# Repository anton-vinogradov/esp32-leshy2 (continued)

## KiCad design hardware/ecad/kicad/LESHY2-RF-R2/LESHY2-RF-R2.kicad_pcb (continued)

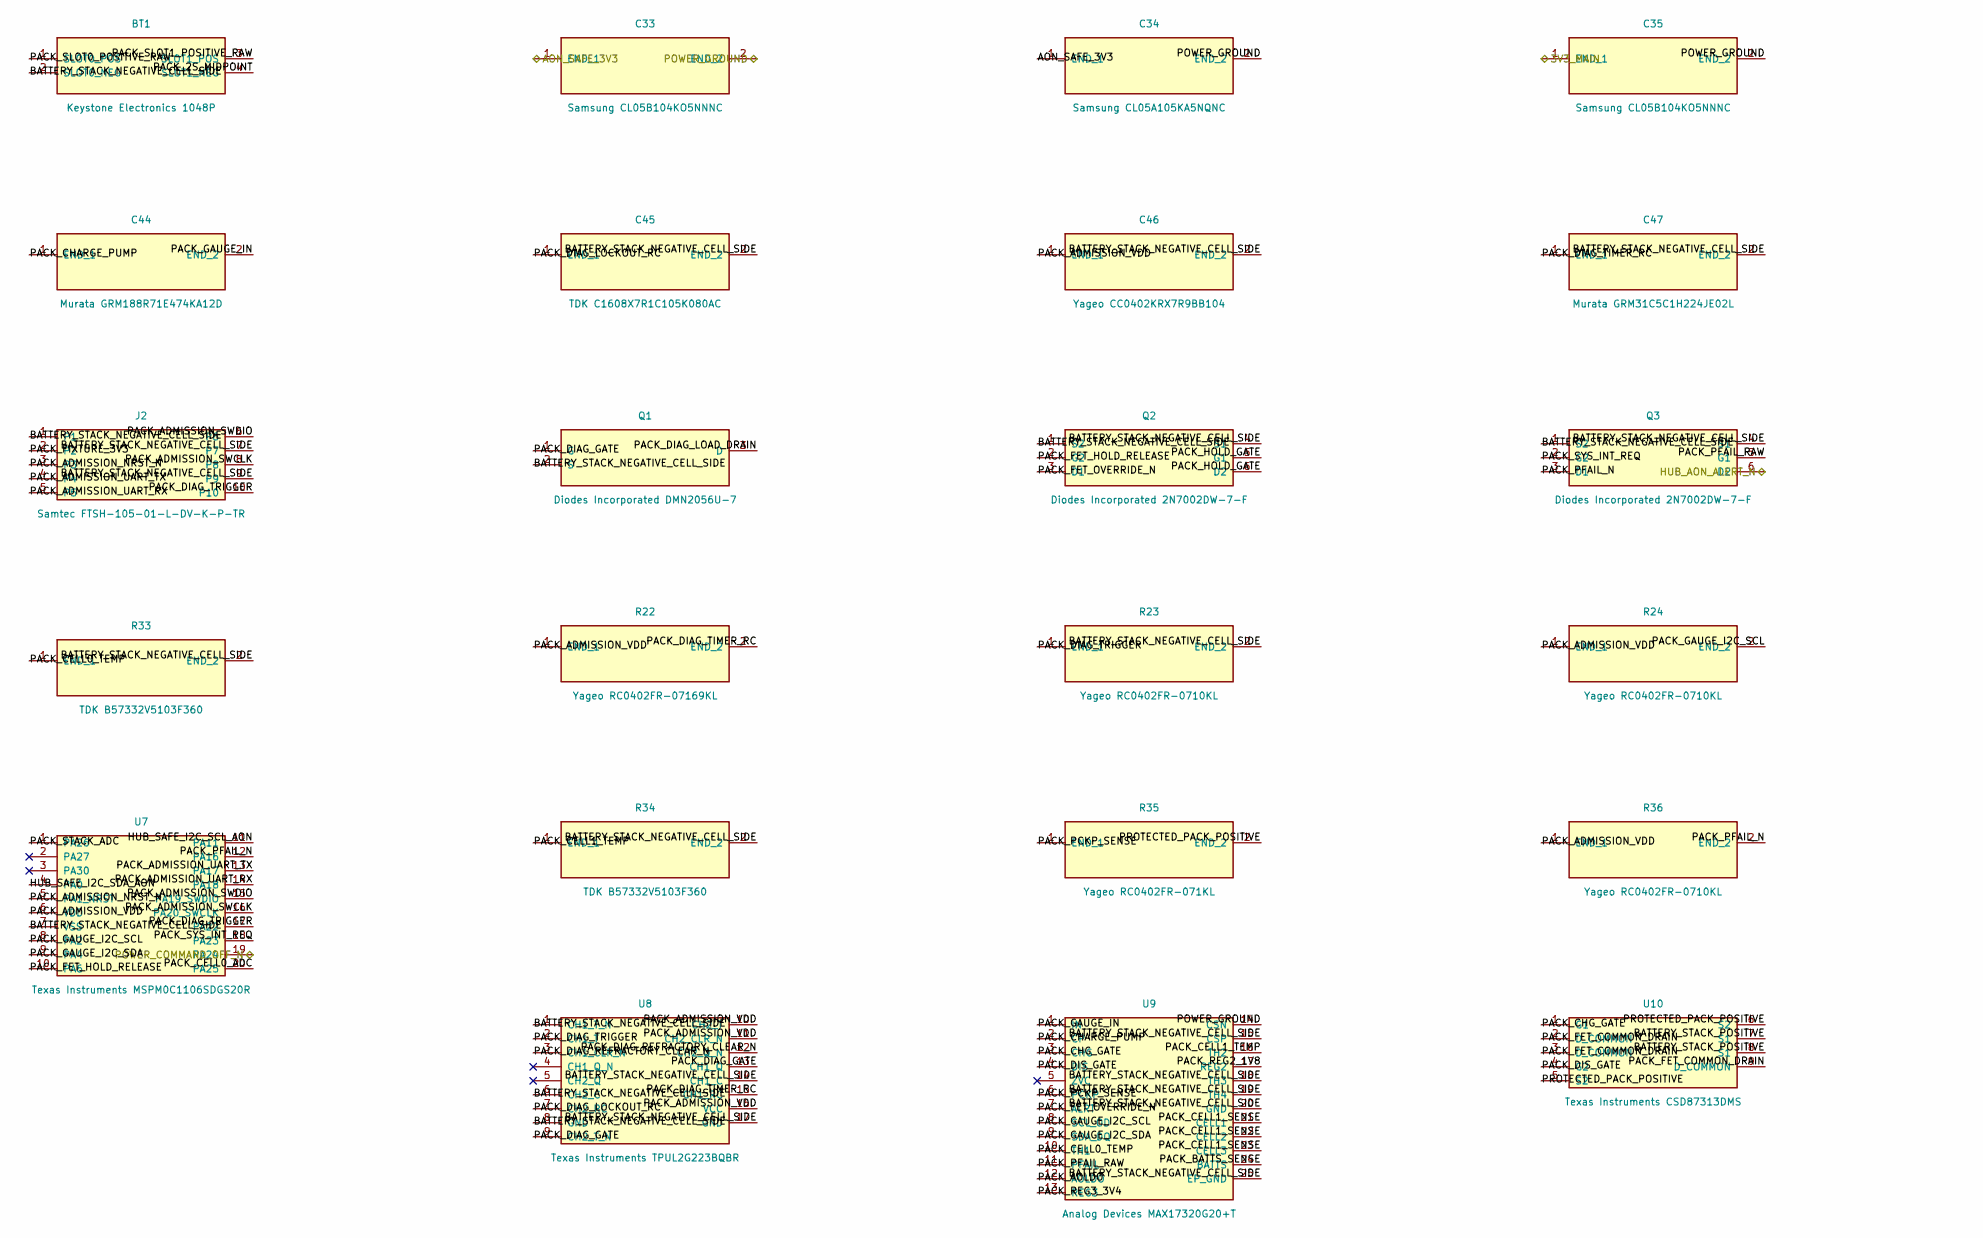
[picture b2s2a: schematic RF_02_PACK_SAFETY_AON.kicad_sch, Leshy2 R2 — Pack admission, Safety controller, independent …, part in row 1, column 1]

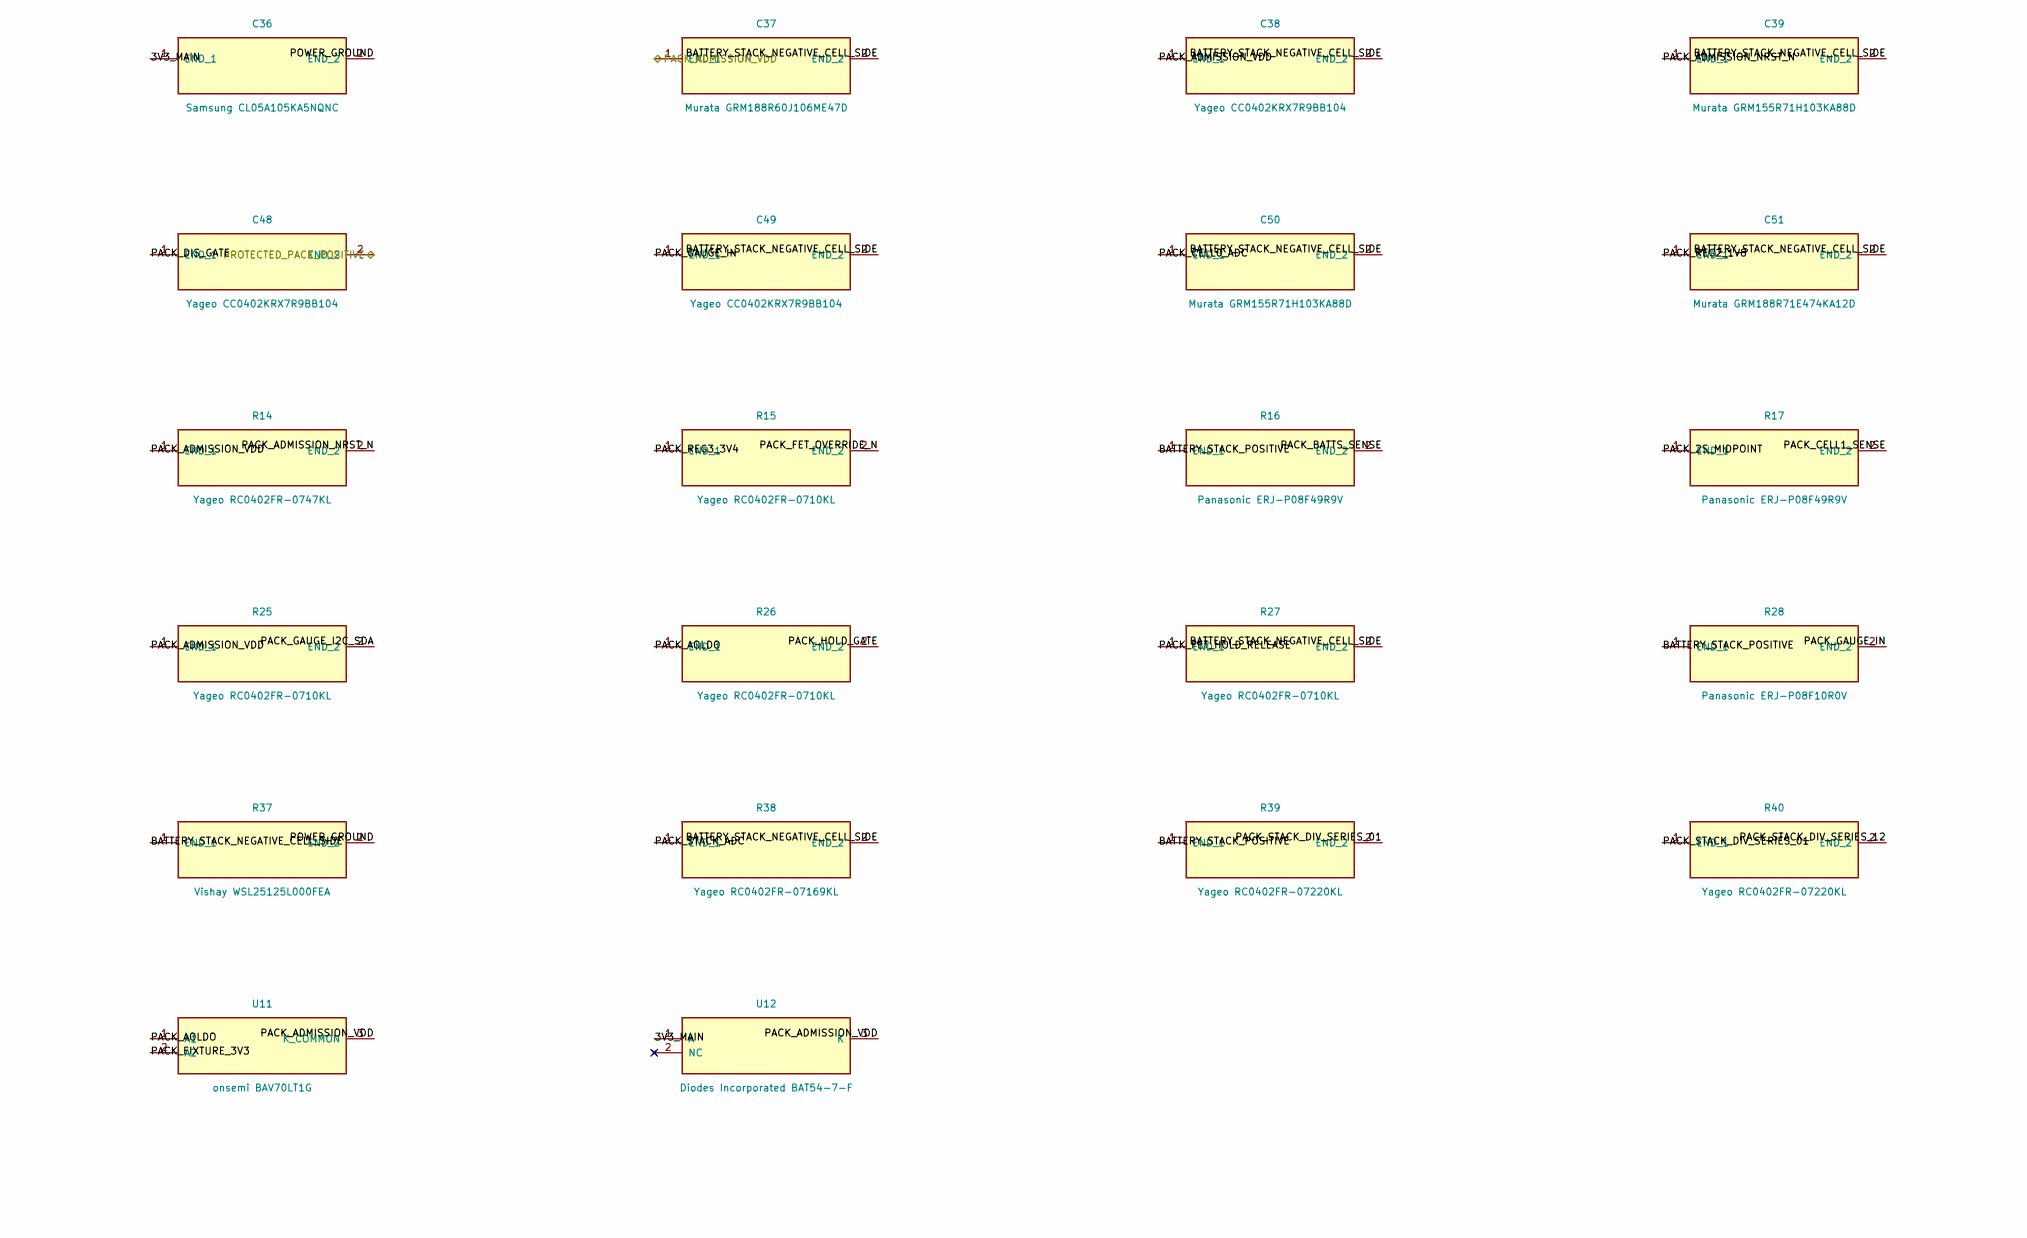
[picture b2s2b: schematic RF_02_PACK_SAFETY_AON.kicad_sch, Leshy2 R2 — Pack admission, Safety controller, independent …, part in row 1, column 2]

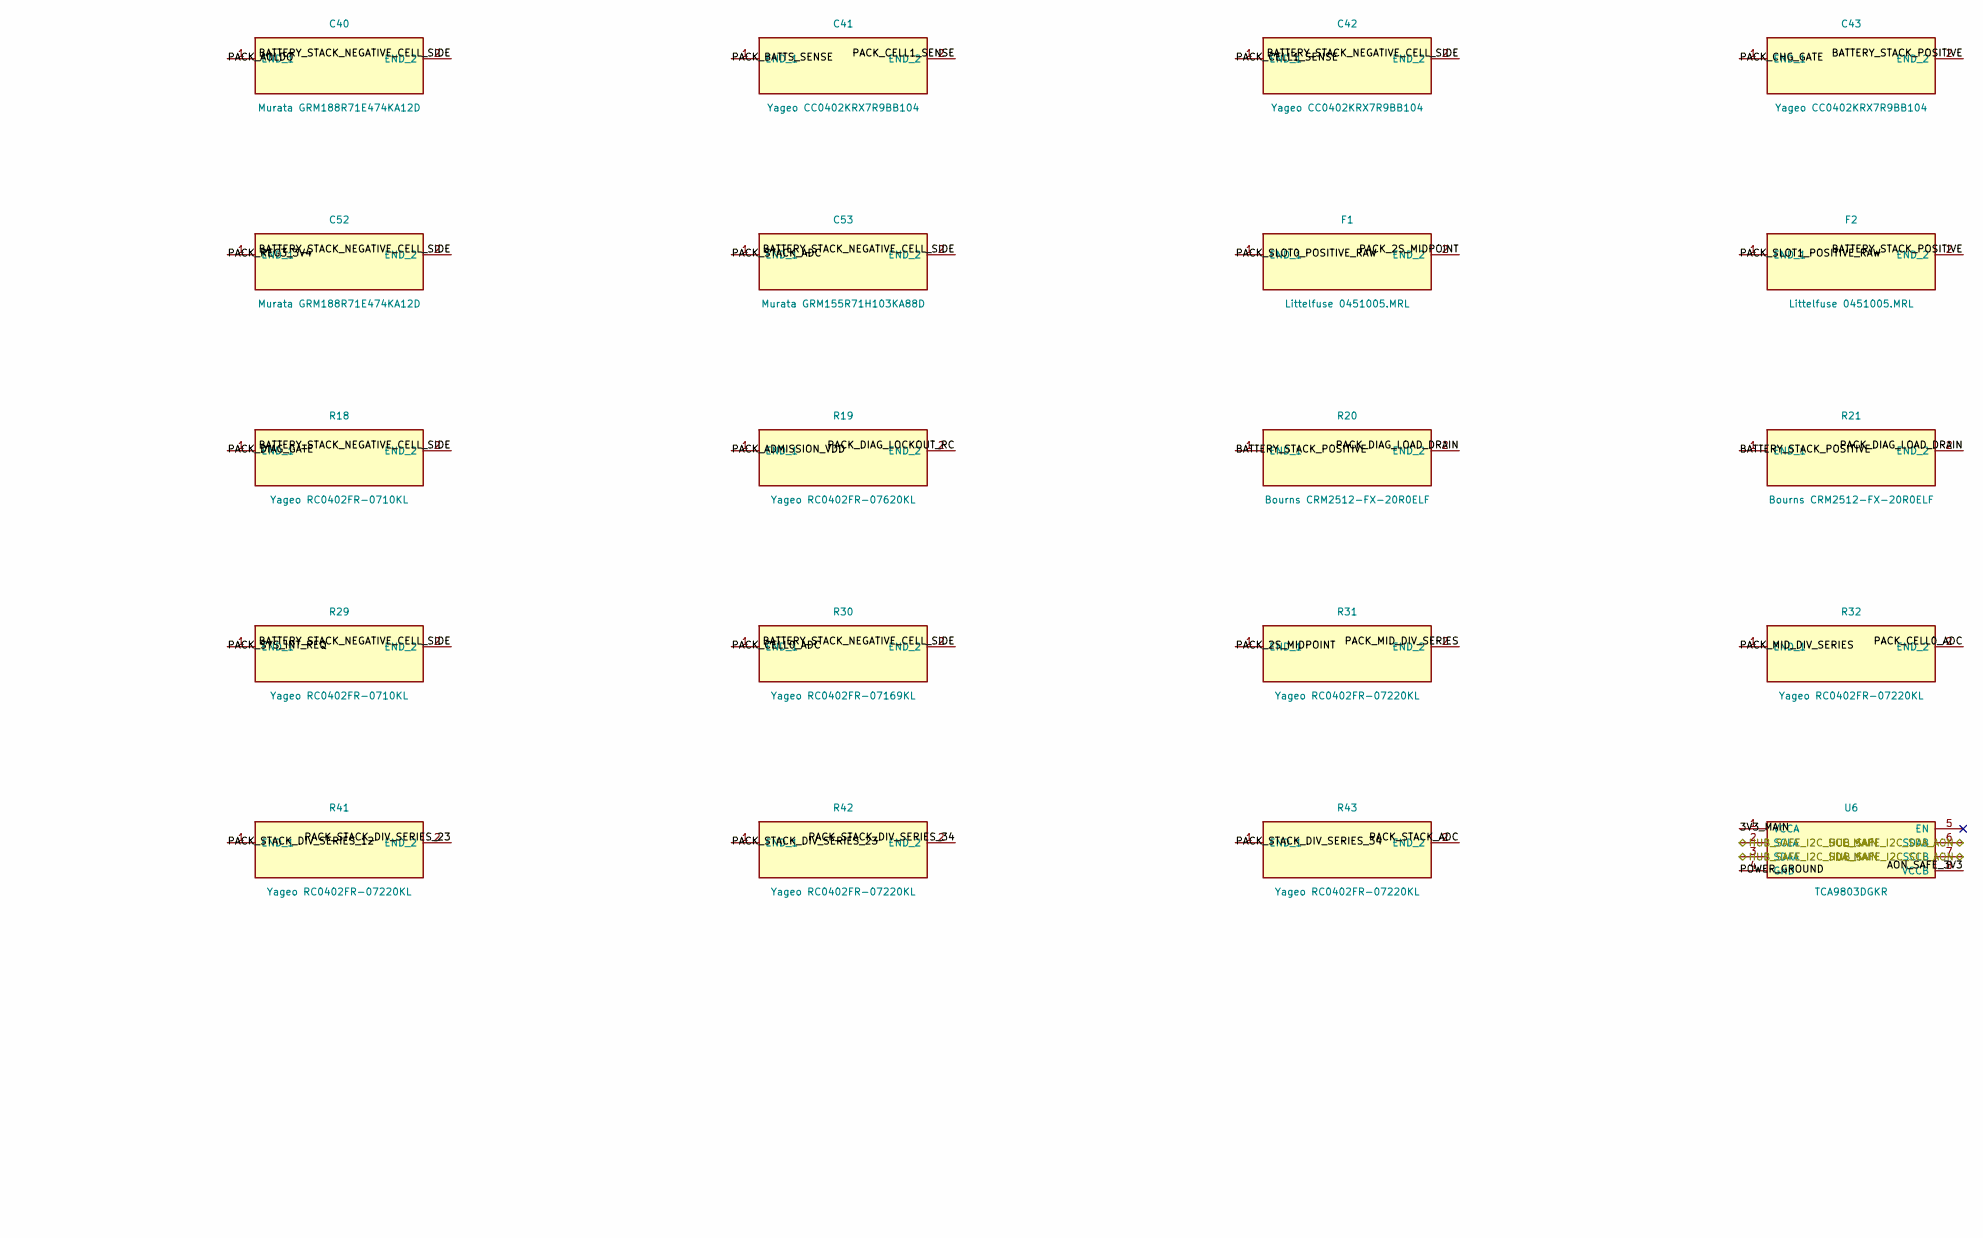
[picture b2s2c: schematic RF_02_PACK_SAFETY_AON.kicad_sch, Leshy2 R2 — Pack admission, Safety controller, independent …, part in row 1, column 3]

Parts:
BT1: Keystone Electronics 1048P; Keystone-1048P-POLARITY-CORRECTED
C33, C35: Samsung CL05B104KO5NNNC; C_0402_1005Metric
C34, C36: Samsung CL05A105KA5NQNC; C_0402_1005Metric
C37: Murata GRM188R60J106ME47D; C_0603_1608Metric
C38, C41, C42, C43, C46, C48, C49: Yageo CC0402KRX7R9BB104; C_0402_1005Metric
C39, C50, C53: Murata GRM155R71H103KA88D; C_0402_1005Metric
C40, C44, C51, C52: Murata GRM188R71E474KA12D; C_0603_1608Metric
C45: TDK C1608X7R1C105K080AC; C_0603_1608Metric
C47: Murata GRM31C5C1H224JE02L; C_1206_3216Metric
F1, F2: Littelfuse 0451005.MRL; 0451005.MRL
J2: Samtec FTSH-105-01-L-DV-K-P-TR; FTSH-105-01-L-DV-K-P-TR
Q1: Diodes Incorporated DMN2056U-7; SOT-23
Q2, Q3: Diodes Incorporated 2N7002DW-7-F; SOT-363_SC-70-6
R14: Yageo RC0402FR-0747KL; R_0402_1005Metric
R15, R18, R23, R24, R25, R26, R27, R29, R36: Yageo RC0402FR-0710KL; R_0402_1005Metric
R16, R17: Panasonic ERJ-P08F49R9V; R_1206_3216Metric
R19: Yageo RC0402FR-07620KL; R_0402_1005Metric
R20, R21: Bourns CRM2512-FX-20R0ELF; R_2512_6332Metric
R22, R30, R38: Yageo RC0402FR-07169KL; R_0402_1005Metric
R28: Panasonic ERJ-P08F10R0V; R_1206_3216Metric
R31, R32, R39, R40, R41, R42, R43: Yageo RC0402FR-07220KL; R_0402_1005Metric
R33, R34: TDK B57332V5103F360; R_0603_1608Metric
R35: Yageo RC0402FR-071KL; R_0402_1005Metric
R37: Vishay WSL25125L000FEA; R_2512_6332Metric
U6: TCA9803DGKR; VSSOP-8_3x3mm_P0.65mm
U7: Texas Instruments MSPM0C1106SDGS20R; Texas_DGS0020A_TSSOP-20_3x5.1mm_P0.5mm
U8: Texas Instruments TPUL2G223BQBR; TPUL2G223BQBR
U9: Analog Devices MAX17320G20+T; TQFN-24-1EP_4x4mm_P0.5mm_EP2.6x2.6mm
U10: Texas Instruments CSD87313DMS; CSD87313DMS
U11: onsemi BAV70LT1G; SOT-23
U12: Diodes Incorporated BAT54-7-F; SOT-23

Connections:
/RF_01_USB_PD_CHARGE/AON_SAFE_3V3: C33.1 (END_1), C34.1 (END_1), U6.8 (VCCB); also elsewhere on the board
/RF_01_USB_PD_CHARGE/POWER_GROUND: C33.2 (END_2), C34.2 (END_2), C35.2 (END_2), C36.2 (END_2), R37.2 (END_2), U6.4 (GND), U9.14 (CSN); also elsewhere on the board
/RF_01_USB_PD_CHARGE/PROTECTED_PACK_POSITIVE: C48.2 (END_2), R35.2 (END_2), U10.5 (S2), U10.6 (S2); also elsewhere on the board
/RF_02_PACK_SAFETY_AON/3V3_MAIN: C35.1 (END_1), C36.1 (END_1), U6.1 (VCCA), U12.1 (A); also elsewhere on the board
/RF_02_PACK_SAFETY_AON/BATTERY_STACK_NEGATIVE_CELL_SIDE: BT1.2 (SLOT0_NEG), C37.2 (END_2), C38.2 (END_2), C39.2 (END_2), C40.2 (END_2), C42.2 (END_2), C45.2 (END_2), C46.2 (END_2), C47.2 (END_2), C49.2 (END_2), C50.2 (END_2), C51.2 (END_2), C52.2 (END_2), C53.2 (END_2), J2.1, J2.7, J2.9, Q1.2 (S), Q2.1 (S2), Q2.4 (S1), Q3.1 (S2), Q3.4 (S1), R18.2 (END_2), R23.2 (END_2), R27.2 (END_2), R29.2 (END_2), R30.2 (END_2), R33.2 (END_2), R34.2 (END_2), R37.1 (END_1), R38.2 (END_2), U7.7 (VSS), U8.1 (CH1_T_N), U8.6 (CH2_C), U8.8 (GND), U8.14 (CH1_C), U8.17 (GND), U9.15 (CSP), U9.18 (TH3), U9.19 (TH4), U9.20 (GND), U9.25 (EP_GND)
/RF_02_PACK_SAFETY_AON/BATTERY_STACK_POSITIVE: C43.2 (END_2), F2.2 (END_2), R16.1 (END_1), R20.1 (END_1), R21.1 (END_1), R28.1 (END_1), R39.1 (END_1), U10.7 (S1), U10.8 (S1)
/RF_02_PACK_SAFETY_AON/HUB_SAFE_I2C_SCL_AON: U6.7 (SCLB), U7.11 (PA11); also elsewhere on the board
/RF_02_PACK_SAFETY_AON/HUB_SAFE_I2C_SCL_MAIN: U6.2 (SCLA); also elsewhere on the board
/RF_02_PACK_SAFETY_AON/HUB_SAFE_I2C_SDA_AON: U6.6 (SDAB), U7.4 (PA0); also elsewhere on the board
/RF_02_PACK_SAFETY_AON/HUB_SAFE_I2C_SDA_MAIN: U6.3 (SDAA); also elsewhere on the board
/RF_02_PACK_SAFETY_AON/PACK_2S_MIDPOINT: BT1.4 (SLOT1_NEG), F1.2 (END_2), R17.1 (END_1), R31.1 (END_1)
/RF_02_PACK_SAFETY_AON/PACK_ADMISSION_NRST_N: C39.1 (END_1), J2.3, R14.2 (END_2), U7.5 (PA1_NRST)
/RF_02_PACK_SAFETY_AON/PACK_ADMISSION_SWCLK: J2.8, U7.16 (PA20_SWCLK)
/RF_02_PACK_SAFETY_AON/PACK_ADMISSION_SWDIO: J2.6, U7.15 (PA19_SWDIO)
/RF_02_PACK_SAFETY_AON/PACK_ADMISSION_UART_RX: J2.5, U7.14 (PA18)
/RF_02_PACK_SAFETY_AON/PACK_ADMISSION_UART_TX: J2.4, U7.13 (PA17)
/RF_02_PACK_SAFETY_AON/PACK_ADMISSION_VDD: C37.1 (END_1), C38.1 (END_1), C46.1 (END_1), R14.1 (END_1), R19.1 (END_1), R22.1 (END_1), R24.1 (END_1), R25.1 (END_1), R36.1 (END_1), U7.6 (VDD), U8.10 (CH2_T), U8.11 (CH2_CLR_N), U8.16 (VCC), U11.3 (K_COMMON), U12.3 (K); also elsewhere on the board
/RF_02_PACK_SAFETY_AON/PACK_AOLDO: C40.1 (END_1), R26.1 (END_1), U9.12 (AOLDO), U11.1 (A1)
/RF_02_PACK_SAFETY_AON/PACK_BATTS_SENSE: C41.1 (END_1), R16.2 (END_2), U9.24 (BATTS)
/RF_02_PACK_SAFETY_AON/PACK_CELL0_ADC: C50.1 (END_1), R30.1 (END_1), R32.2 (END_2), U7.20 (PA25)
/RF_02_PACK_SAFETY_AON/PACK_CELL0_TEMP: R33.1 (END_1), U9.10 (TH1)
/RF_02_PACK_SAFETY_AON/PACK_CELL1_SENSE: C41.2 (END_2), C42.1 (END_1), R17.2 (END_2), U9.21 (CELL1), U9.22 (CELL2), U9.23 (CELL3)
/RF_02_PACK_SAFETY_AON/PACK_CELL1_TEMP: R34.1 (END_1), U9.16 (TH2)
/RF_02_PACK_SAFETY_AON/PACK_CHARGE_PUMP: C44.1 (END_1), U9.2 (CP)
/RF_02_PACK_SAFETY_AON/PACK_CHG_GATE: C43.1 (END_1), U9.3 (CHG), U10.1 (G1)
/RF_02_PACK_SAFETY_AON/PACK_DIAG_GATE: Q1.1 (G), R18.1 (END_1), U8.9 (CH2_T_N), U8.13 (CH1_Q)
/RF_02_PACK_SAFETY_AON/PACK_DIAG_LOAD_DRAIN: Q1.3 (D), R20.2 (END_2), R21.2 (END_2)
/RF_02_PACK_SAFETY_AON/PACK_DIAG_LOCKOUT_RC: C45.1 (END_1), R19.2 (END_2), U8.7 (CH2_RC)
/RF_02_PACK_SAFETY_AON/PACK_DIAG_REFRACTORY_CLEAR_N: U8.3 (CH1_CLR_N), U8.12 (CH2_Q_N)
/RF_02_PACK_SAFETY_AON/PACK_DIAG_TIMER_RC: C47.1 (END_1), R22.2 (END_2), U8.15 (CH1_RC)
/RF_02_PACK_SAFETY_AON/PACK_DIAG_TRIGGER: J2.10, R23.1 (END_1), U7.17 (PA22), U8.2 (CH1_T)
/RF_02_PACK_SAFETY_AON/PACK_DIS_GATE: C48.1 (END_1), U9.4 (DIS), U10.4 (G2)
/RF_02_PACK_SAFETY_AON/PACK_FET_COMMON_DRAIN: U10.2 (D_COMMON), U10.3 (D_COMMON), U10.9 (D_COMMON)
/RF_02_PACK_SAFETY_AON/PACK_FET_HOLD_RELEASE: Q2.2 (G2), R27.1 (END_1), U7.10 (PA6)
/RF_02_PACK_SAFETY_AON/PACK_FET_OVERRIDE_N: Q2.3 (D1), R15.2 (END_2), U9.7 (ALRT)
/RF_02_PACK_SAFETY_AON/PACK_FIXTURE_3V3: J2.2, U11.2 (A2)
/RF_02_PACK_SAFETY_AON/PACK_GAUGE_I2C_SCL: R24.2 (END_2), U7.8 (PA2), U9.8 (SCL_OD)
/RF_02_PACK_SAFETY_AON/PACK_GAUGE_I2C_SDA: R25.2 (END_2), U7.9 (PA4), U9.9 (SDA_DQ)
/RF_02_PACK_SAFETY_AON/PACK_GAUGE_IN: C44.2 (END_2), C49.1 (END_1), R28.2 (END_2), U9.1 (IN)
/RF_02_PACK_SAFETY_AON/PACK_HOLD_GATE: Q2.5 (G1), Q2.6 (D2), R26.2 (END_2)
/RF_02_PACK_SAFETY_AON/PACK_MID_DIV_SERIES: R31.2 (END_2), R32.1 (END_1)
/RF_02_PACK_SAFETY_AON/PACK_PCKP_SENSE: R35.1 (END_1), U9.6 (PCKP)
/RF_02_PACK_SAFETY_AON/PACK_PFAIL_N: Q3.3 (D1), R36.2 (END_2), U7.12 (PA16)
/RF_02_PACK_SAFETY_AON/PACK_PFAIL_RAW: Q3.5 (G1), U9.11 (PFAIL)
/RF_02_PACK_SAFETY_AON/PACK_REG2_1V8: C51.1 (END_1), U9.17 (REG2)
/RF_02_PACK_SAFETY_AON/PACK_REG3_3V4: C52.1 (END_1), R15.1 (END_1), U9.13 (REG3)
/RF_02_PACK_SAFETY_AON/PACK_SLOT0_POSITIVE_RAW: BT1.1 (SLOT0_POS), F1.1 (END_1)
/RF_02_PACK_SAFETY_AON/PACK_SLOT1_POSITIVE_RAW: BT1.3 (SLOT1_POS), F2.1 (END_1)
/RF_02_PACK_SAFETY_AON/PACK_STACK_ADC: C53.1 (END_1), R38.1 (END_1), R43.2 (END_2), U7.1 (PA26)
/RF_02_PACK_SAFETY_AON/PACK_STACK_DIV_SERIES_01: R39.2 (END_2), R40.1 (END_1)
/RF_02_PACK_SAFETY_AON/PACK_STACK_DIV_SERIES_12: R40.2 (END_2), R41.1 (END_1)
/RF_02_PACK_SAFETY_AON/PACK_STACK_DIV_SERIES_23: R41.2 (END_2), R42.1 (END_1)
/RF_02_PACK_SAFETY_AON/PACK_STACK_DIV_SERIES_34: R42.2 (END_2), R43.1 (END_1)
/RF_02_PACK_SAFETY_AON/PACK_SYS_INT_REQ: Q3.2 (G2), R29.1 (END_1), U7.18 (PA23)
/RF_50_TX_SAFETY_EVIDENCE/HUB_AON_ALERT_N: Q3.6 (D2); also elsewhere on the board
/RF_50_TX_SAFETY_EVIDENCE/POWER_COMMAND_OFF_N: U7.19 (PA24); also elsewhere on the board
